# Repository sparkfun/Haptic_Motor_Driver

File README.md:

SparkFun Haptic Motor Driver
========================================

[*SparkFun Haptic Motor Driver (ROB-14538)*](https://www.sparkfun.com/products/14538)
	
Ready to add some good vibes to your project? Look no further than the SparkFun Haptic Motor Driver. This board breaks out Texas Instruments' DRV2605L Haptic Motor Driver, which adds meaningful feedback from your devices using the breakout and an Arduino-compatible device.

The DRV2605L is capable of driving two different types of motors, ERM and LRA. It is important to know, however, that the default firmware for the DRV2605L is set for use with ERM type motors. We have created an Arduino library that makes the DRV2605L easy to use with six different ERM effects and one LRA effect.
	
The SparkFun Haptic Motor Driver breakout board features six pins to provide power to the sensor and I2C bus. Additionally, a microcontroller that supports I2C is required to communicate with the DRV2605L and relay the data to the user by means of vibration.

Repository Contents	
---------------	

* **/Documentation** - Data sheets, additional product information, ZIP folder containing all project files and a ZIP folder containing libraries and example code 
* **/Hardware** - Eagle design files (.brd, .sch)
* **/Libraries** - Libraries for use with the Haptic Motor Driver with some example projects 
* **/Production** - Production panel files (.brd)

Documentation
---------------	

* **[Library](https://github.com/sparkfun/SparkFun_Haptic_Motor_Driver_Arduino_Library)** - Arduino-compatible library for the Haptic Motor Driver.
* **[Hookup Guide](https://learn.sparkfun.com/tutorials/haptic-motor-driver-hook-up-guide)** - Basic hookup guide for the Haptic Motor driver.
* **[SparkFun Fritzing repo](https://github.com/sparkfun/Fritzing_Parts)** - Fritzing diagrams for SparkFun products.

Product Versions
---------------

* [ROB-14538](https://www.sparkfun.com/products/retired/14538)- v20
* [ROB-14031](https://www.sparkfun.com/products/retired/14031)- v10

Version History
---------------

* [v20](https://github.com/sparkfun/Haptic_Motor_Driver/releases/tag/v20) - v20
* [v10](https://github.com/sparkfun/Haptic_Motor_Driver/releases/tag/v10) - Initial release

License Information
---------------

This product is _**open source**_! 

Please review the LICENSE.md file for license information. 

If you have any questions or concerns on licensing, please contact techsupport@sparkfun.com.

Distributed as-is; no warranty is given.

- Your friends at SparkFun.

_<COLLABORATION CREDIT>_

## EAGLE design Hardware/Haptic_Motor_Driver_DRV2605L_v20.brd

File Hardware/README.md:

SparkFun DRV2605L Haptic Motor Driver Design Files
=====================================

The .sch and .brd files hare are Eagle CAD schematic and PCB design files from SparkFun Electronics.
A freeware version of Eagle can be found [here](http://www.cadsoftusa.com/download-eagle/freeware/).

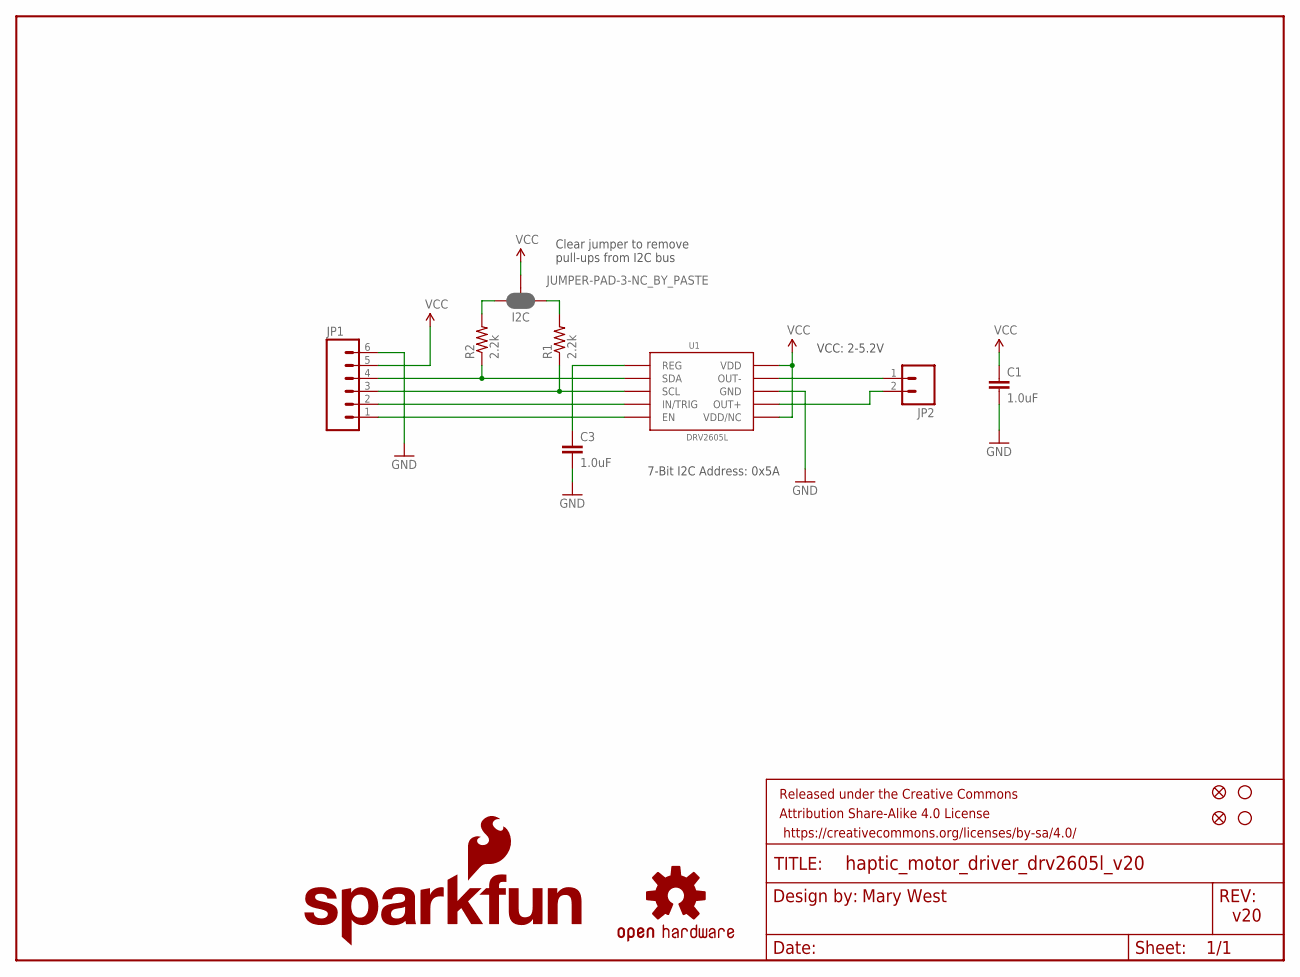
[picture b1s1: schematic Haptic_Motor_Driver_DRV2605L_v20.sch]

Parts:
C1, C3: 1.0uF; 0402-CAP
FID1, FID2: FIDUCIAL1X2; FIDUCIAL-1X2
FRAME2: FRAME-LETTER; CREATIVE_COMMONS
I2C: JUMPER-PAD-3-NC_BY_PASTE; PAD-JUMPER-3-NC_BY_PASTE_YES_SILK_FULL_BOX
JP1: M06SILK_FEMALE_PTH; 1X06
JP2: M02PTH; 1X02
LOGO2: OSHW-LOGOS; OSHW-LOGO-S
LOGO4: SFE_LOGO_NAME_FLAME.1_INCH; SFE_LOGO_NAME_FLAME_.1
R1, R2: 2.2k; 0603-RES
STANDOFF1, STANDOFF4: STAND-OFF
U1: DRV2605L; VSSOP-10

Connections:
GND: C1.2, C3.2, JP1.6, U1.P$8 (GND)
unnamed: JP1.4, R2.1, U1.P$3 (SDA)
unnamed: JP1.3, R1.1, U1.P$2 (SCL)
unnamed: C3.1, U1.P$1 (REG)
unnamed: JP1.2, U1.P$4 (IN/TRIG)
unnamed: JP1.1, U1.P$5 (EN)
unnamed: JP2.1, U1.P$9 (OUT-)
unnamed: JP2.2, U1.P$7 (OUT+)
unnamed: I2C.3, R2.2
unnamed: I2C.1, R1.2
VCC: C1.1, I2C.2, JP1.5, U1.P$6 (VDD/NC), U1.P$10 (VDD)

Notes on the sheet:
7-Bit I2C Address: 0x5A
VCC: 2-5.2V
Clear jumper to remove pull-ups from I2C bus
v20
Mary West

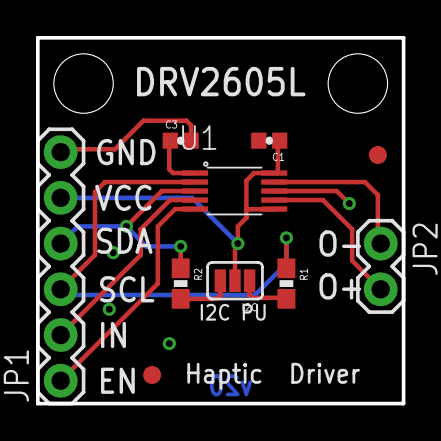
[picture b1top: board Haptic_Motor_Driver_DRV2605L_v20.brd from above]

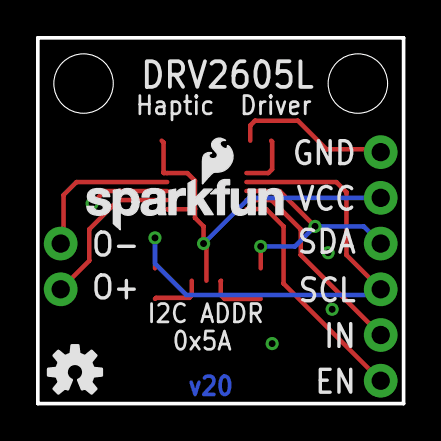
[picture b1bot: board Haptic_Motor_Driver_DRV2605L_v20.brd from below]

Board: 2 copper layers, 20.3 x 20.3 mm, 15 parts (2 on the bottom side), 11 nets.

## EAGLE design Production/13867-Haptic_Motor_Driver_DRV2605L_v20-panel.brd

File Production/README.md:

SparkFun DRV2605L Haptic Motor Driver Production Files
=========================================

These are the production files SparkFun uses for printing PCBs.

License Information
-------------------
This product is open source! 

The hardware is released under [Creative Commons ShareAlike 4.0 International](https://creativecommons.org/licenses/by-sa/4.0/).

Please use, reuse, and modify these files as you see fit. Please maintain attribution to SparkFun Electronics and release anything derivative under the same license.

Distributed as-is; no warranty is given.

- Your friends at SparkFun.

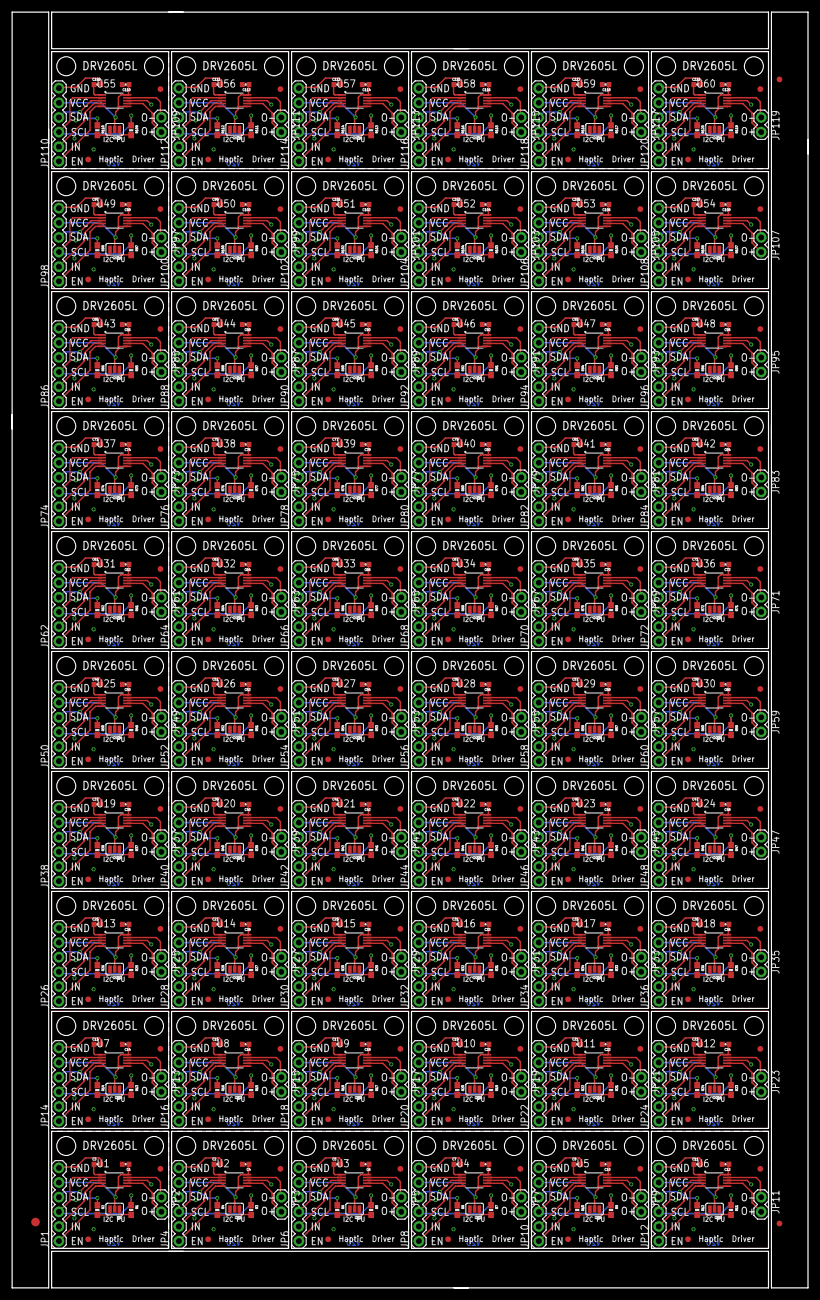
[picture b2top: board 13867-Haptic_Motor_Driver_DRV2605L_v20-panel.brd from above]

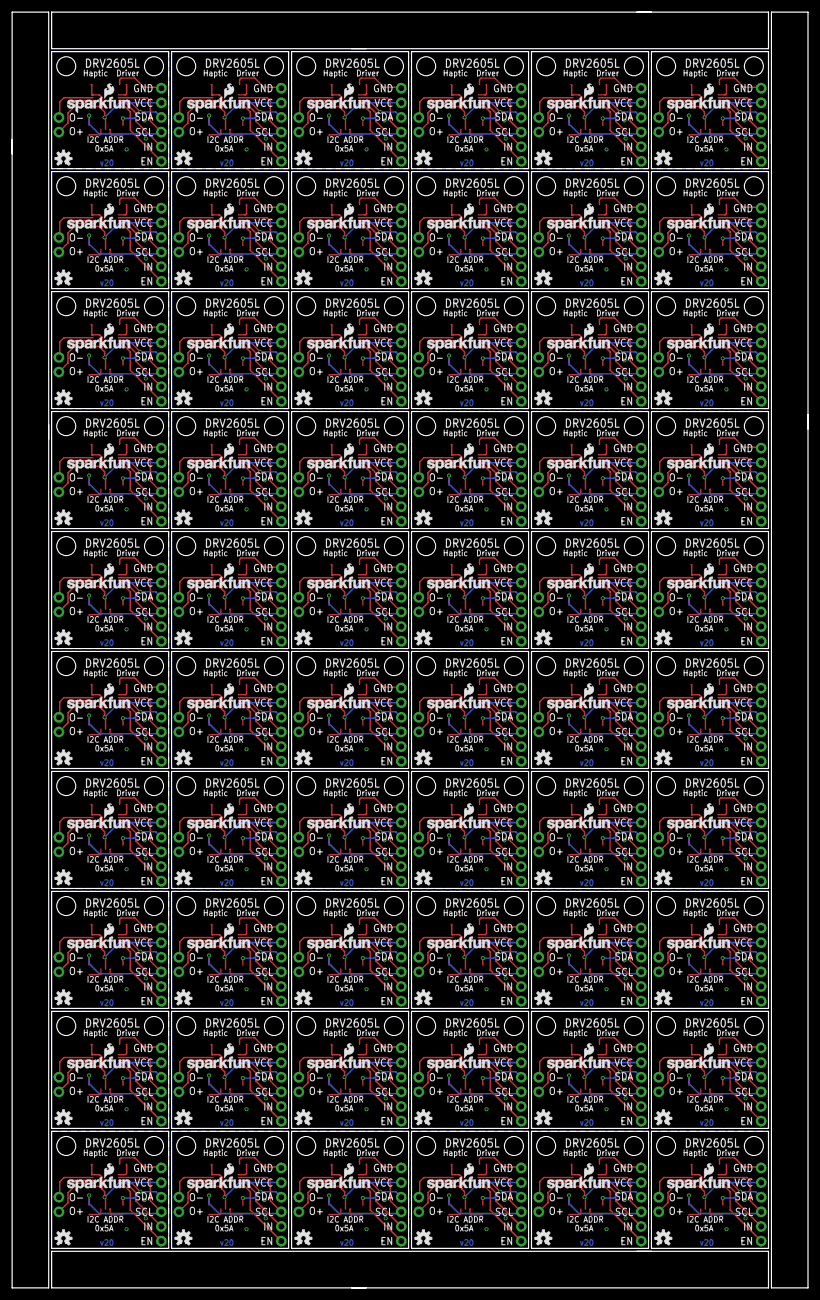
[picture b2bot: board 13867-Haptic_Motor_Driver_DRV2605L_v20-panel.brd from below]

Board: 2 copper layers, 138.2 x 221.5 mm, 843 parts (120 on the bottom side), 660 nets.

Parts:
C1, C2, C3, C4, C5, C6, C7, C8, C9, C10, C11, C12, C13, C14, C15, C16, C17, C18, C19, C20, C21, C22, C23, C24, C25, C26, C27, C28, C29, C30, C31, C32, C33, C34, C35, C36, C37, C38, C39, C40, C41, C42, C43, C44, C45, C46, C47, C48, C49, C50, C51, C52, C53, C54, C55, C56, C57, C58, C59, C60, C61, C62, C63, C64, C65, C66, C67, C68, C69, C70, C71, C72, C73, C74, C75, C76, C77, C78, C79, C80, C81, C82, C83, C84, C85, C86, C87, C88, C89, C90, C91, C92, C93, C94, C95, C96, C97, C98, C99, C100, C101, C102, C103, C104, C105, C106, C107, C108, C109, C110, C111, C112, C113, C114, C115, C116, C117, C118, C119, C120: 1.0uF; 0402-CAP
E$1: FIDUCIAL-1.5X3
E$5, E$6: FIDUCIAL-1X2
FID1, FID2, FID3, FID4, FID5, FID6, FID7, FID8, FID9, FID10, FID11, FID12, FID13, FID14, FID15, FID16, FID17, FID18, FID19, FID20, FID21, FID22, FID23, FID24, FID25, FID26, FID27, FID28, FID29, FID30, FID31, FID32, FID33, FID34, FID35, FID36, FID37, FID38, FID39, FID40, FID41, FID42, FID43, FID44, FID45, FID46, FID47, FID48, FID49, FID50, FID51, FID52, FID53, FID54, FID55, FID56, FID57, FID58, FID59, FID60, FID61, FID62, FID63, FID64, FID65, FID66, FID67, FID68, FID69, FID70, FID71, FID72, FID73, FID74, FID75, FID76, FID77, FID78, FID79, FID80, FID81, FID82, FID83, FID84, FID85, FID86, FID87, FID88, FID89, FID90, FID91, FID92, FID93, FID94, FID95, FID96, FID97, FID98, FID99, FID100, FID101, FID102, FID103, FID104, FID105, FID106, FID107, FID108, FID109, FID110, FID111, FID112, FID113, FID114, FID115, FID116, FID117, FID118, FID119, FID120: FIDUCIAL1X2; FIDUCIAL-1X2
I2C, I2C1, I2C2, I2C3, I2C4, I2C5, I2C6, I2C7, I2C8, I2C9, I2C10, I2C11, I2C12, I2C13, I2C14, I2C15, I2C16, I2C17, I2C18, I2C19, I2C20, I2C21, I2C22, I2C23, I2C24, I2C25, I2C26, I2C27, I2C28, I2C29, I2C30, I2C31, I2C32, I2C33, I2C34, I2C35, I2C36, I2C37, I2C38, I2C39, I2C40, I2C41, I2C42, I2C43, I2C44, I2C45, I2C46, I2C47, I2C48, I2C49, I2C50, I2C51, I2C52, I2C53, I2C54, I2C55, I2C56, I2C57, I2C58, I2C59: JUMPER-PAD-3-NC_BY_PASTE; PAD-JUMPER-3-NC_BY_PASTE_YES_SILK_FULL_BOX
JP1, JP4, JP6, JP8, JP10, JP12, JP14, JP16, JP18, JP20, JP22, JP24, JP26, JP28, JP30, JP32, JP34, JP36, JP38, JP40, JP42, JP44, JP46, JP48, JP50, JP52, JP54, JP56, JP58, JP60, JP62, JP64, JP66, JP68, JP70, JP72, JP74, JP76, JP78, JP80, JP82, JP84, JP86, JP88, JP90, JP92, JP94, JP96, JP98, JP100, JP102, JP104, JP106, JP108, JP110, JP112, JP114, JP116, JP118, JP120: 1X06
JP2, JP3, JP5, JP7, JP9, JP11, JP13, JP15, JP17, JP19, JP21, JP23, JP25, JP27, JP29, JP31, JP33, JP35, JP37, JP39, JP41, JP43, JP45, JP47, JP49, JP51, JP53, JP55, JP57, JP59, JP61, JP63, JP65, JP67, JP69, JP71, JP73, JP75, JP77, JP79, JP81, JP83, JP85, JP87, JP89, JP91, JP93, JP95, JP97, JP99, JP101, JP103, JP105, JP107, JP109, JP111, JP113, JP115, JP117, JP119: 1X02
LOGO1, LOGO2, LOGO5, LOGO7, LOGO9, LOGO11, LOGO13, LOGO15, LOGO17, LOGO19, LOGO21, LOGO23, LOGO25, LOGO27, LOGO29, LOGO31, LOGO33, LOGO35, LOGO37, LOGO39, LOGO41, LOGO43, LOGO45, LOGO47, LOGO49, LOGO51, LOGO53, LOGO55, LOGO57, LOGO59, LOGO61, LOGO63, LOGO65, LOGO67, LOGO69, LOGO71, LOGO73, LOGO75, LOGO77, LOGO79, LOGO81, LOGO83, LOGO85, LOGO87, LOGO89, LOGO91, LOGO93, LOGO95, LOGO97, LOGO99, LOGO101, LOGO103, LOGO105, LOGO107, LOGO109, LOGO111, LOGO113, LOGO115, LOGO117, LOGO119: OSHW-LOGOS; OSHW-LOGO-S
LOGO3, LOGO4, LOGO6, LOGO8, LOGO10, LOGO12, LOGO14, LOGO16, LOGO18, LOGO20, LOGO22, LOGO24, LOGO26, LOGO28, LOGO30, LOGO32, LOGO34, LOGO36, LOGO38, LOGO40, LOGO42, LOGO44, LOGO46, LOGO48, LOGO50, LOGO52, LOGO54, LOGO56, LOGO58, LOGO60, LOGO62, LOGO64, LOGO66, LOGO68, LOGO70, LOGO72, LOGO74, LOGO76, LOGO78, LOGO80, LOGO82, LOGO84, LOGO86, LOGO88, LOGO90, LOGO92, LOGO94, LOGO96, LOGO98, LOGO100, LOGO102, LOGO104, LOGO106, LOGO108, LOGO110, LOGO112, LOGO114, LOGO116, LOGO118, LOGO120: SFE_LOGO_NAME_FLAME.1_INCH; SFE_LOGO_NAME_FLAME_.1
R1, R2, R3, R4, R5, R6, R7, R8, R9, R10, R11, R12, R13, R14, R15, R16, R17, R18, R19, R20, R21, R22, R23, R24, R25, R26, R27, R28, R29, R30, R31, R32, R33, R34, R35, R36, R37, R38, R39, R40, R41, R42, R43, R44, R45, R46, R47, R48, R49, R50, R51, R52, R53, R54, R55, R56, R57, R58, R59, R60, R61, R62, R63, R64, R65, R66, R67, R68, R69, R70, R71, R72, R73, R74, R75, R76, R77, R78, R79, R80, R81, R82, R83, R84, R85, R86, R87, R88, R89, R90, R91, R92, R93, R94, R95, R96, R97, R98, R99, R100, R101, R102, R103, R104, R105, R106, R107, R108, R109, R110, R111, R112, R113, R114, R115, R116, R117, R118, R119, R120: 2.2k; 0603-RES
STANDOFF1, STANDOFF2, STANDOFF3, STANDOFF4, STANDOFF5, STANDOFF6, STANDOFF7, STANDOFF8, STANDOFF9, STANDOFF10, STANDOFF11, STANDOFF12, STANDOFF13, STANDOFF14, STANDOFF15, STANDOFF16, STANDOFF17, STANDOFF18, STANDOFF19, STANDOFF20, STANDOFF21, STANDOFF22, STANDOFF23, STANDOFF24, STANDOFF25, STANDOFF26, STANDOFF27, STANDOFF28, STANDOFF29, STANDOFF30, STANDOFF31, STANDOFF32, STANDOFF33, STANDOFF34, STANDOFF35, STANDOFF36, STANDOFF37, STANDOFF38, STANDOFF39, STANDOFF40, STANDOFF41, STANDOFF42, STANDOFF43, STANDOFF44, STANDOFF45, STANDOFF46, STANDOFF47, STANDOFF48, STANDOFF49, STANDOFF50, STANDOFF51, STANDOFF52, STANDOFF53, STANDOFF54, STANDOFF55, STANDOFF56, STANDOFF57, STANDOFF58, STANDOFF59, STANDOFF60, STANDOFF61, STANDOFF62, STANDOFF63, STANDOFF64, STANDOFF65, STANDOFF66, STANDOFF67, STANDOFF68, STANDOFF69, STANDOFF70, STANDOFF71, STANDOFF72, STANDOFF73, STANDOFF74, STANDOFF75, STANDOFF76, STANDOFF77, STANDOFF78, STANDOFF79, STANDOFF80, STANDOFF81, STANDOFF82, STANDOFF83, STANDOFF84, STANDOFF85, STANDOFF86, STANDOFF87, STANDOFF88, STANDOFF89, STANDOFF90, STANDOFF91, STANDOFF92, STANDOFF93, STANDOFF94, STANDOFF95, STANDOFF96, STANDOFF97, STANDOFF98, STANDOFF99, STANDOFF100, STANDOFF101, STANDOFF102, STANDOFF103, STANDOFF104, STANDOFF105, STANDOFF106, STANDOFF107, STANDOFF108, STANDOFF109, STANDOFF110, STANDOFF111, STANDOFF112, STANDOFF113, STANDOFF114, STANDOFF115, STANDOFF116, STANDOFF117, STANDOFF118, STANDOFF119, STANDOFF120: STAND-OFF
U1, U2, U3, U4, U5, U6, U7, U8, U9, U10, U11, U12, U13, U14, U15, U16, U17, U18, U19, U20, U21, U22, U23, U24, U25, U26, U27, U28, U29, U30, U31, U32, U33, U34, U35, U36, U37, U38, U39, U40, U41, U42, U43, U44, U45, U46, U47, U48, U49, U50, U51, U52, U53, U54, U55, U56, U57, U58, U59, U60: DRV2605L; VSSOP-10

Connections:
GND: C1.2, C3.2, JP1.6, U1.P$8
GND1: C2.2, C4.2, JP4.6, U2.P$8
GND2: C5.2, C6.2, JP6.6, U3.P$8
GND3: C7.2, C8.2, JP8.6, U4.P$8
GND4: C9.2, C10.2, JP10.6, U5.P$8
GND5: C11.2, C12.2, JP12.6, U6.P$8
GND6: C13.2, C14.2, JP14.6, U7.P$8
GND7: C15.2, C16.2, JP16.6, U8.P$8
GND8: C17.2, C18.2, JP18.6, U9.P$8
GND9: C19.2, C20.2, JP20.6, U10.P$8
GND10: C21.2, C22.2, JP22.6, U11.P$8
GND11: C23.2, C24.2, JP24.6, U12.P$8
GND12: C25.2, C26.2, JP26.6, U13.P$8
GND13: C27.2, C28.2, JP28.6, U14.P$8
GND14: C29.2, C30.2, JP30.6, U15.P$8
GND15: C31.2, C32.2, JP32.6, U16.P$8
GND16: C33.2, C34.2, JP34.6, U17.P$8
GND17: C35.2, C36.2, JP36.6, U18.P$8
GND18: C37.2, C38.2, JP38.6, U19.P$8
GND19: C39.2, C40.2, JP40.6, U20.P$8
GND20: C41.2, C42.2, JP42.6, U21.P$8
GND21: C43.2, C44.2, JP44.6, U22.P$8
GND22: C45.2, C46.2, JP46.6, U23.P$8
GND23: C47.2, C48.2, JP48.6, U24.P$8
GND24: C49.2, C50.2, JP50.6, U25.P$8
GND25: C51.2, C52.2, JP52.6, U26.P$8
GND26: C53.2, C54.2, JP54.6, U27.P$8
GND27: C55.2, C56.2, JP56.6, U28.P$8
GND28: C57.2, C58.2, JP58.6, U29.P$8
GND29: C59.2, C60.2, JP60.6, U30.P$8
GND30: C61.2, C62.2, JP62.6, U31.P$8
GND31: C63.2, C64.2, JP64.6, U32.P$8
GND32: C65.2, C66.2, JP66.6, U33.P$8
GND33: C67.2, C68.2, JP68.6, U34.P$8
GND34: C69.2, C70.2, JP70.6, U35.P$8
GND35: C71.2, C72.2, JP72.6, U36.P$8
GND36: C73.2, C74.2, JP74.6, U37.P$8
GND37: C75.2, C76.2, JP76.6, U38.P$8
GND38: C77.2, C78.2, JP78.6, U39.P$8
GND39: C79.2, C80.2, JP80.6, U40.P$8
GND40: C81.2, C82.2, JP82.6, U41.P$8
GND41: C83.2, C84.2, JP84.6, U42.P$8
GND42: C85.2, C86.2, JP86.6, U43.P$8
GND43: C87.2, C88.2, JP88.6, U44.P$8
GND44: C89.2, C90.2, JP90.6, U45.P$8
GND45: C91.2, C92.2, JP92.6, U46.P$8
GND46: C93.2, C94.2, JP94.6, U47.P$8
GND47: C95.2, C96.2, JP96.6, U48.P$8
GND48: C97.2, C98.2, JP98.6, U49.P$8
GND49: C99.2, C100.2, JP100.6, U50.P$8
GND50: C101.2, C102.2, JP102.6, U51.P$8
GND51: C103.2, C104.2, JP104.6, U52.P$8
GND52: C105.2, C106.2, JP106.6, U53.P$8
GND53: C107.2, C108.2, JP108.6, U54.P$8
GND54: C109.2, C110.2, JP110.6, U55.P$8
GND55: C111.2, C112.2, JP112.6, U56.P$8
GND56: C113.2, C114.2, JP114.6, U57.P$8
GND57: C115.2, C116.2, JP116.6, U58.P$8
GND58: C117.2, C118.2, JP118.6, U59.P$8
GND59: C119.2, C120.2, JP120.6, U60.P$8
unnamed: JP1.4, R2.1, U1.P$3
unnamed: JP1.3, R1.1, U1.P$2
unnamed: C3.1, U1.P$1
unnamed: JP1.2, U1.P$4
unnamed: JP1.1, U1.P$5
unnamed: JP2.1, U1.P$9
unnamed: JP2.2, U1.P$7
unnamed: I2C.3, R2.2
unnamed: I2C.1, R1.2
unnamed: C2.1, U2.P$1
unnamed: JP4.2, U2.P$4
unnamed: JP4.1, U2.P$5
unnamed: JP3.1, U2.P$9
unnamed: JP3.2, U2.P$7
unnamed: I2C1.3, R4.2
unnamed: I2C1.1, R3.2
unnamed: JP4.4, R4.1, U2.P$3
unnamed: JP4.3, R3.1, U2.P$2
unnamed: C5.1, U3.P$1
unnamed: JP6.2, U3.P$4
unnamed: JP6.1, U3.P$5
unnamed: JP5.1, U3.P$9
unnamed: JP5.2, U3.P$7
unnamed: I2C2.3, R6.2
unnamed: I2C2.1, R5.2
unnamed: JP6.4, R6.1, U3.P$3
unnamed: JP6.3, R5.1, U3.P$2
unnamed: C7.1, U4.P$1
unnamed: JP8.2, U4.P$4
unnamed: JP8.1, U4.P$5
unnamed: JP7.1, U4.P$9
unnamed: JP7.2, U4.P$7
unnamed: I2C3.3, R8.2
unnamed: I2C3.1, R7.2
unnamed: JP8.4, R8.1, U4.P$3
unnamed: JP8.3, R7.1, U4.P$2
unnamed: C9.1, U5.P$1
unnamed: JP10.2, U5.P$4
unnamed: JP10.1, U5.P$5
unnamed: JP9.1, U5.P$9
unnamed: JP9.2, U5.P$7
unnamed: I2C4.3, R10.2
unnamed: I2C4.1, R9.2
unnamed: JP10.4, R10.1, U5.P$3
unnamed: JP10.3, R9.1, U5.P$2
unnamed: C11.1, U6.P$1
unnamed: JP12.2, U6.P$4
unnamed: JP12.1, U6.P$5
unnamed: JP11.1, U6.P$9
unnamed: JP11.2, U6.P$7
unnamed: I2C5.3, R12.2
unnamed: I2C5.1, R11.2
unnamed: JP12.4, R12.1, U6.P$3
unnamed: JP12.3, R11.1, U6.P$2
unnamed: C13.1, U7.P$1
unnamed: JP14.2, U7.P$4
unnamed: JP14.1, U7.P$5
unnamed: JP13.1, U7.P$9
unnamed: JP13.2, U7.P$7
unnamed: I2C6.3, R14.2
unnamed: I2C6.1, R13.2
unnamed: JP14.4, R14.1, U7.P$3
unnamed: JP14.3, R13.1, U7.P$2
unnamed: C15.1, U8.P$1
unnamed: JP16.2, U8.P$4
unnamed: JP16.1, U8.P$5
unnamed: JP15.1, U8.P$9
unnamed: JP15.2, U8.P$7
unnamed: I2C7.3, R16.2
unnamed: I2C7.1, R15.2
unnamed: JP16.4, R16.1, U8.P$3
unnamed: JP16.3, R15.1, U8.P$2
unnamed: C17.1, U9.P$1
unnamed: JP18.2, U9.P$4
unnamed: JP18.1, U9.P$5
unnamed: JP17.1, U9.P$9
unnamed: JP17.2, U9.P$7
unnamed: I2C8.3, R18.2
unnamed: I2C8.1, R17.2
unnamed: JP18.4, R18.1, U9.P$3
unnamed: JP18.3, R17.1, U9.P$2
unnamed: C19.1, U10.P$1
unnamed: JP20.2, U10.P$4
unnamed: JP20.1, U10.P$5
unnamed: JP19.1, U10.P$9
unnamed: JP19.2, U10.P$7
unnamed: I2C9.3, R20.2
unnamed: I2C9.1, R19.2
unnamed: JP20.4, R20.1, U10.P$3
unnamed: JP20.3, R19.1, U10.P$2
unnamed: C21.1, U11.P$1
unnamed: JP22.2, U11.P$4
unnamed: JP22.1, U11.P$5
unnamed: JP21.1, U11.P$9
unnamed: JP21.2, U11.P$7
unnamed: I2C10.3, R22.2
unnamed: I2C10.1, R21.2
unnamed: JP22.4, R22.1, U11.P$3
unnamed: JP22.3, R21.1, U11.P$2
unnamed: C23.1, U12.P$1
unnamed: JP24.2, U12.P$4
unnamed: JP24.1, U12.P$5
unnamed: JP23.1, U12.P$9
unnamed: JP23.2, U12.P$7
unnamed: I2C11.3, R24.2
unnamed: I2C11.1, R23.2
unnamed: JP24.4, R24.1, U12.P$3
unnamed: JP24.3, R23.1, U12.P$2
unnamed: C25.1, U13.P$1
unnamed: JP26.2, U13.P$4
unnamed: JP26.1, U13.P$5
unnamed: JP25.1, U13.P$9
unnamed: JP25.2, U13.P$7
unnamed: I2C12.3, R26.2
unnamed: I2C12.1, R25.2
unnamed: JP26.4, R26.1, U13.P$3
unnamed: JP26.3, R25.1, U13.P$2
unnamed: C27.1, U14.P$1
unnamed: JP28.2, U14.P$4
unnamed: JP28.1, U14.P$5
unnamed: JP27.1, U14.P$9
unnamed: JP27.2, U14.P$7
unnamed: I2C13.3, R28.2
unnamed: I2C13.1, R27.2
unnamed: JP28.4, R28.1, U14.P$3
unnamed: JP28.3, R27.1, U14.P$2
unnamed: C29.1, U15.P$1
unnamed: JP30.2, U15.P$4
unnamed: JP30.1, U15.P$5
unnamed: JP29.1, U15.P$9
unnamed: JP29.2, U15.P$7
unnamed: I2C14.3, R30.2
unnamed: I2C14.1, R29.2
unnamed: JP30.4, R30.1, U15.P$3
unnamed: JP30.3, R29.1, U15.P$2
unnamed: C31.1, U16.P$1
unnamed: JP32.2, U16.P$4
unnamed: JP32.1, U16.P$5
unnamed: JP31.1, U16.P$9
unnamed: JP31.2, U16.P$7
unnamed: I2C15.3, R32.2
unnamed: I2C15.1, R31.2
unnamed: JP32.4, R32.1, U16.P$3
unnamed: JP32.3, R31.1, U16.P$2
unnamed: C33.1, U17.P$1
unnamed: JP34.2, U17.P$4
unnamed: JP34.1, U17.P$5
unnamed: JP33.1, U17.P$9
unnamed: JP33.2, U17.P$7
unnamed: I2C16.3, R34.2
unnamed: I2C16.1, R33.2
unnamed: JP34.4, R34.1, U17.P$3
unnamed: JP34.3, R33.1, U17.P$2
unnamed: C35.1, U18.P$1
unnamed: JP36.2, U18.P$4
unnamed: JP36.1, U18.P$5
unnamed: JP35.1, U18.P$9
unnamed: JP35.2, U18.P$7
unnamed: I2C17.3, R36.2
unnamed: I2C17.1, R35.2
unnamed: JP36.4, R36.1, U18.P$3
unnamed: JP36.3, R35.1, U18.P$2
unnamed: C37.1, U19.P$1
unnamed: JP38.2, U19.P$4
unnamed: JP38.1, U19.P$5
unnamed: JP37.1, U19.P$9
unnamed: JP37.2, U19.P$7
unnamed: I2C18.3, R38.2
unnamed: I2C18.1, R37.2
unnamed: JP38.4, R38.1, U19.P$3
unnamed: JP38.3, R37.1, U19.P$2
unnamed: C39.1, U20.P$1
unnamed: JP40.2, U20.P$4
unnamed: JP40.1, U20.P$5
unnamed: JP39.1, U20.P$9
unnamed: JP39.2, U20.P$7
unnamed: I2C19.3, R40.2
unnamed: I2C19.1, R39.2
unnamed: JP40.4, R40.1, U20.P$3
unnamed: JP40.3, R39.1, U20.P$2
unnamed: C41.1, U21.P$1
unnamed: JP42.2, U21.P$4
unnamed: JP42.1, U21.P$5
unnamed: JP41.1, U21.P$9
unnamed: JP41.2, U21.P$7
unnamed: I2C20.3, R42.2
unnamed: I2C20.1, R41.2
unnamed: JP42.4, R42.1, U21.P$3
unnamed: JP42.3, R41.1, U21.P$2
unnamed: C43.1, U22.P$1
unnamed: JP44.2, U22.P$4
unnamed: JP44.1, U22.P$5
unnamed: JP43.1, U22.P$9
unnamed: JP43.2, U22.P$7
unnamed: I2C21.3, R44.2
unnamed: I2C21.1, R43.2
unnamed: JP44.4, R44.1, U22.P$3
unnamed: JP44.3, R43.1, U22.P$2
unnamed: C45.1, U23.P$1
unnamed: JP46.2, U23.P$4
unnamed: JP46.1, U23.P$5
unnamed: JP45.1, U23.P$9
unnamed: JP45.2, U23.P$7
unnamed: I2C22.3, R46.2
unnamed: I2C22.1, R45.2
unnamed: JP46.4, R46.1, U23.P$3
unnamed: JP46.3, R45.1, U23.P$2
unnamed: C47.1, U24.P$1
unnamed: JP48.2, U24.P$4
unnamed: JP48.1, U24.P$5
unnamed: JP47.1, U24.P$9
unnamed: JP47.2, U24.P$7
unnamed: I2C23.3, R48.2
unnamed: I2C23.1, R47.2
unnamed: JP48.4, R48.1, U24.P$3
unnamed: JP48.3, R47.1, U24.P$2
unnamed: C49.1, U25.P$1
unnamed: JP50.2, U25.P$4
unnamed: JP50.1, U25.P$5
unnamed: JP49.1, U25.P$9
unnamed: JP49.2, U25.P$7
unnamed: I2C24.3, R50.2
unnamed: I2C24.1, R49.2
unnamed: JP50.4, R50.1, U25.P$3
unnamed: JP50.3, R49.1, U25.P$2
unnamed: C51.1, U26.P$1
unnamed: JP52.2, U26.P$4
unnamed: JP52.1, U26.P$5
unnamed: JP51.1, U26.P$9
unnamed: JP51.2, U26.P$7
unnamed: I2C25.3, R52.2
unnamed: I2C25.1, R51.2
unnamed: JP52.4, R52.1, U26.P$3
unnamed: JP52.3, R51.1, U26.P$2
unnamed: C53.1, U27.P$1
unnamed: JP54.2, U27.P$4
unnamed: JP54.1, U27.P$5
unnamed: JP53.1, U27.P$9
unnamed: JP53.2, U27.P$7
unnamed: I2C26.3, R54.2
unnamed: I2C26.1, R53.2
unnamed: JP54.4, R54.1, U27.P$3
unnamed: JP54.3, R53.1, U27.P$2
unnamed: C55.1, U28.P$1
unnamed: JP56.2, U28.P$4
unnamed: JP56.1, U28.P$5
unnamed: JP55.1, U28.P$9
unnamed: JP55.2, U28.P$7
unnamed: I2C27.3, R56.2
unnamed: I2C27.1, R55.2
unnamed: JP56.4, R56.1, U28.P$3
unnamed: JP56.3, R55.1, U28.P$2
unnamed: C57.1, U29.P$1
unnamed: JP58.2, U29.P$4
unnamed: JP58.1, U29.P$5
unnamed: JP57.1, U29.P$9
unnamed: JP57.2, U29.P$7
unnamed: I2C28.3, R58.2
unnamed: I2C28.1, R57.2
unnamed: JP58.4, R58.1, U29.P$3
unnamed: JP58.3, R57.1, U29.P$2
unnamed: C59.1, U30.P$1
unnamed: JP60.2, U30.P$4
unnamed: JP60.1, U30.P$5
unnamed: JP59.1, U30.P$9
unnamed: JP59.2, U30.P$7
unnamed: I2C29.3, R60.2
unnamed: I2C29.1, R59.2
unnamed: JP60.4, R60.1, U30.P$3
unnamed: JP60.3, R59.1, U30.P$2
unnamed: C61.1, U31.P$1
unnamed: JP62.2, U31.P$4
unnamed: JP62.1, U31.P$5
unnamed: JP61.1, U31.P$9
unnamed: JP61.2, U31.P$7
unnamed: I2C30.3, R62.2
unnamed: I2C30.1, R61.2
unnamed: JP62.4, R62.1, U31.P$3
unnamed: JP62.3, R61.1, U31.P$2
unnamed: C63.1, U32.P$1
unnamed: JP64.2, U32.P$4
unnamed: JP64.1, U32.P$5
unnamed: JP63.1, U32.P$9
unnamed: JP63.2, U32.P$7
unnamed: I2C31.3, R64.2
unnamed: I2C31.1, R63.2
unnamed: JP64.4, R64.1, U32.P$3
unnamed: JP64.3, R63.1, U32.P$2
unnamed: C65.1, U33.P$1
unnamed: JP66.2, U33.P$4
unnamed: JP66.1, U33.P$5
unnamed: JP65.1, U33.P$9
unnamed: JP65.2, U33.P$7
unnamed: I2C32.3, R66.2
unnamed: I2C32.1, R65.2
unnamed: JP66.4, R66.1, U33.P$3
unnamed: JP66.3, R65.1, U33.P$2
unnamed: C67.1, U34.P$1
unnamed: JP68.2, U34.P$4
unnamed: JP68.1, U34.P$5
unnamed: JP67.1, U34.P$9
unnamed: JP67.2, U34.P$7
unnamed: I2C33.3, R68.2
unnamed: I2C33.1, R67.2
unnamed: JP68.4, R68.1, U34.P$3
unnamed: JP68.3, R67.1, U34.P$2
unnamed: C69.1, U35.P$1
unnamed: JP70.2, U35.P$4
unnamed: JP70.1, U35.P$5
unnamed: JP69.1, U35.P$9
unnamed: JP69.2, U35.P$7
unnamed: I2C34.3, R70.2
unnamed: I2C34.1, R69.2
unnamed: JP70.4, R70.1, U35.P$3
unnamed: JP70.3, R69.1, U35.P$2
unnamed: C71.1, U36.P$1
unnamed: JP72.2, U36.P$4
unnamed: JP72.1, U36.P$5
unnamed: JP71.1, U36.P$9
unnamed: JP71.2, U36.P$7
unnamed: I2C35.3, R72.2
unnamed: I2C35.1, R71.2
unnamed: JP72.4, R72.1, U36.P$3
unnamed: JP72.3, R71.1, U36.P$2
unnamed: C73.1, U37.P$1
unnamed: JP74.2, U37.P$4
unnamed: JP74.1, U37.P$5
unnamed: JP73.1, U37.P$9
unnamed: JP73.2, U37.P$7
unnamed: I2C36.3, R74.2
unnamed: I2C36.1, R73.2
unnamed: JP74.4, R74.1, U37.P$3
unnamed: JP74.3, R73.1, U37.P$2
unnamed: C75.1, U38.P$1
unnamed: JP76.2, U38.P$4
unnamed: JP76.1, U38.P$5
unnamed: JP75.1, U38.P$9
unnamed: JP75.2, U38.P$7
unnamed: I2C37.3, R76.2
unnamed: I2C37.1, R75.2
unnamed: JP76.4, R76.1, U38.P$3
unnamed: JP76.3, R75.1, U38.P$2
unnamed: C77.1, U39.P$1
unnamed: JP78.2, U39.P$4
unnamed: JP78.1, U39.P$5
unnamed: JP77.1, U39.P$9
unnamed: JP77.2, U39.P$7
unnamed: I2C38.3, R78.2
unnamed: I2C38.1, R77.2
unnamed: JP78.4, R78.1, U39.P$3
unnamed: JP78.3, R77.1, U39.P$2
unnamed: C79.1, U40.P$1
unnamed: JP80.2, U40.P$4
unnamed: JP80.1, U40.P$5
unnamed: JP79.1, U40.P$9
unnamed: JP79.2, U40.P$7
unnamed: I2C39.3, R80.2
unnamed: I2C39.1, R79.2
unnamed: JP80.4, R80.1, U40.P$3
unnamed: JP80.3, R79.1, U40.P$2
unnamed: C81.1, U41.P$1
unnamed: JP82.2, U41.P$4
unnamed: JP82.1, U41.P$5
unnamed: JP81.1, U41.P$9
unnamed: JP81.2, U41.P$7
unnamed: I2C40.3, R82.2
unnamed: I2C40.1, R81.2
unnamed: JP82.4, R82.1, U41.P$3
unnamed: JP82.3, R81.1, U41.P$2
unnamed: C83.1, U42.P$1
unnamed: JP84.2, U42.P$4
unnamed: JP84.1, U42.P$5
unnamed: JP83.1, U42.P$9
unnamed: JP83.2, U42.P$7
unnamed: I2C41.3, R84.2
unnamed: I2C41.1, R83.2
unnamed: JP84.4, R84.1, U42.P$3
unnamed: JP84.3, R83.1, U42.P$2
unnamed: C85.1, U43.P$1
unnamed: JP86.2, U43.P$4
unnamed: JP86.1, U43.P$5
unnamed: JP85.1, U43.P$9
unnamed: JP85.2, U43.P$7
unnamed: I2C42.3, R86.2
unnamed: I2C42.1, R85.2
unnamed: JP86.4, R86.1, U43.P$3
unnamed: JP86.3, R85.1, U43.P$2
unnamed: C87.1, U44.P$1
unnamed: JP88.2, U44.P$4
unnamed: JP88.1, U44.P$5
unnamed: JP87.1, U44.P$9
unnamed: JP87.2, U44.P$7
unnamed: I2C43.3, R88.2
unnamed: I2C43.1, R87.2
unnamed: JP88.4, R88.1, U44.P$3
unnamed: JP88.3, R87.1, U44.P$2
unnamed: C89.1, U45.P$1
unnamed: JP90.2, U45.P$4
unnamed: JP90.1, U45.P$5
unnamed: JP89.1, U45.P$9
unnamed: JP89.2, U45.P$7
unnamed: I2C44.3, R90.2
unnamed: I2C44.1, R89.2
unnamed: JP90.4, R90.1, U45.P$3
unnamed: JP90.3, R89.1, U45.P$2
unnamed: C91.1, U46.P$1
unnamed: JP92.2, U46.P$4
unnamed: JP92.1, U46.P$5
unnamed: JP91.1, U46.P$9
unnamed: JP91.2, U46.P$7
unnamed: I2C45.3, R92.2
unnamed: I2C45.1, R91.2
unnamed: JP92.4, R92.1, U46.P$3
unnamed: JP92.3, R91.1, U46.P$2
unnamed: C93.1, U47.P$1
unnamed: JP94.2, U47.P$4
unnamed: JP94.1, U47.P$5
unnamed: JP93.1, U47.P$9
unnamed: JP93.2, U47.P$7
unnamed: I2C46.3, R94.2
unnamed: I2C46.1, R93.2
unnamed: JP94.4, R94.1, U47.P$3
unnamed: JP94.3, R93.1, U47.P$2
unnamed: C95.1, U48.P$1
unnamed: JP96.2, U48.P$4
unnamed: JP96.1, U48.P$5
unnamed: JP95.1, U48.P$9
unnamed: JP95.2, U48.P$7
unnamed: I2C47.3, R96.2
unnamed: I2C47.1, R95.2
unnamed: JP96.4, R96.1, U48.P$3
unnamed: JP96.3, R95.1, U48.P$2
unnamed: C97.1, U49.P$1
unnamed: JP98.2, U49.P$4
unnamed: JP98.1, U49.P$5
unnamed: JP97.1, U49.P$9
unnamed: JP97.2, U49.P$7
unnamed: I2C48.3, R98.2
unnamed: I2C48.1, R97.2
unnamed: JP98.4, R98.1, U49.P$3
unnamed: JP98.3, R97.1, U49.P$2
unnamed: C99.1, U50.P$1
unnamed: JP100.2, U50.P$4
unnamed: JP100.1, U50.P$5
unnamed: JP99.1, U50.P$9
unnamed: JP99.2, U50.P$7
unnamed: I2C49.3, R100.2
unnamed: I2C49.1, R99.2
unnamed: JP100.4, R100.1, U50.P$3
unnamed: JP100.3, R99.1, U50.P$2
unnamed: C101.1, U51.P$1
unnamed: JP102.2, U51.P$4
unnamed: JP102.1, U51.P$5
unnamed: JP101.1, U51.P$9
unnamed: JP101.2, U51.P$7
unnamed: I2C50.3, R102.2
unnamed: I2C50.1, R101.2
unnamed: JP102.4, R102.1, U51.P$3
unnamed: JP102.3, R101.1, U51.P$2
unnamed: C103.1, U52.P$1
unnamed: JP104.2, U52.P$4
unnamed: JP104.1, U52.P$5
unnamed: JP103.1, U52.P$9
unnamed: JP103.2, U52.P$7
unnamed: I2C51.3, R104.2
unnamed: I2C51.1, R103.2
unnamed: JP104.4, R104.1, U52.P$3
unnamed: JP104.3, R103.1, U52.P$2
unnamed: C105.1, U53.P$1
unnamed: JP106.2, U53.P$4
unnamed: JP106.1, U53.P$5
unnamed: JP105.1, U53.P$9
unnamed: JP105.2, U53.P$7
unnamed: I2C52.3, R106.2
unnamed: I2C52.1, R105.2
unnamed: JP106.4, R106.1, U53.P$3
unnamed: JP106.3, R105.1, U53.P$2
unnamed: C107.1, U54.P$1
unnamed: JP108.2, U54.P$4
unnamed: JP108.1, U54.P$5
unnamed: JP107.1, U54.P$9
unnamed: JP107.2, U54.P$7
unnamed: I2C53.3, R108.2
unnamed: I2C53.1, R107.2
unnamed: JP108.4, R108.1, U54.P$3
unnamed: JP108.3, R107.1, U54.P$2
unnamed: C109.1, U55.P$1
unnamed: JP110.2, U55.P$4
unnamed: JP110.1, U55.P$5
unnamed: JP109.1, U55.P$9
unnamed: JP109.2, U55.P$7
unnamed: I2C54.3, R110.2
unnamed: I2C54.1, R109.2
unnamed: JP110.4, R110.1, U55.P$3
unnamed: JP110.3, R109.1, U55.P$2
unnamed: C111.1, U56.P$1
unnamed: JP112.2, U56.P$4
unnamed: JP112.1, U56.P$5
unnamed: JP111.1, U56.P$9
unnamed: JP111.2, U56.P$7
unnamed: I2C55.3, R112.2
unnamed: I2C55.1, R111.2
unnamed: JP112.4, R112.1, U56.P$3
unnamed: JP112.3, R111.1, U56.P$2
unnamed: C113.1, U57.P$1
unnamed: JP114.2, U57.P$4
unnamed: JP114.1, U57.P$5
unnamed: JP113.1, U57.P$9
unnamed: JP113.2, U57.P$7
unnamed: I2C56.3, R114.2
unnamed: I2C56.1, R113.2
unnamed: JP114.4, R114.1, U57.P$3
unnamed: JP114.3, R113.1, U57.P$2
unnamed: C115.1, U58.P$1
unnamed: JP116.2, U58.P$4
unnamed: JP116.1, U58.P$5
unnamed: JP115.1, U58.P$9
unnamed: JP115.2, U58.P$7
unnamed: I2C57.3, R116.2
unnamed: I2C57.1, R115.2
unnamed: JP116.4, R116.1, U58.P$3
unnamed: JP116.3, R115.1, U58.P$2
unnamed: C117.1, U59.P$1
unnamed: JP118.2, U59.P$4
unnamed: JP118.1, U59.P$5
unnamed: JP117.1, U59.P$9
unnamed: JP117.2, U59.P$7
unnamed: I2C58.3, R118.2
unnamed: I2C58.1, R117.2
unnamed: JP118.4, R118.1, U59.P$3
unnamed: JP118.3, R117.1, U59.P$2
unnamed: C119.1, U60.P$1
unnamed: JP120.2, U60.P$4
unnamed: JP120.1, U60.P$5
unnamed: JP119.1, U60.P$9
unnamed: JP119.2, U60.P$7
unnamed: I2C59.3, R120.2
unnamed: I2C59.1, R119.2
unnamed: JP120.4, R120.1, U60.P$3
unnamed: JP120.3, R119.1, U60.P$2
VCC: C1.1, I2C.2, JP1.5, U1.P$6, U1.P$10
VCC1: C4.1, I2C1.2, JP4.5, U2.P$6, U2.P$10
VCC2: C6.1, I2C2.2, JP6.5, U3.P$6, U3.P$10
VCC3: C8.1, I2C3.2, JP8.5, U4.P$6, U4.P$10
VCC4: C10.1, I2C4.2, JP10.5, U5.P$6, U5.P$10
VCC5: C12.1, I2C5.2, JP12.5, U6.P$6, U6.P$10
VCC6: C14.1, I2C6.2, JP14.5, U7.P$6, U7.P$10
VCC7: C16.1, I2C7.2, JP16.5, U8.P$6, U8.P$10
VCC8: C18.1, I2C8.2, JP18.5, U9.P$6, U9.P$10
VCC9: C20.1, I2C9.2, JP20.5, U10.P$6, U10.P$10
VCC10: C22.1, I2C10.2, JP22.5, U11.P$6, U11.P$10
VCC11: C24.1, I2C11.2, JP24.5, U12.P$6, U12.P$10
VCC12: C26.1, I2C12.2, JP26.5, U13.P$6, U13.P$10
VCC13: C28.1, I2C13.2, JP28.5, U14.P$6, U14.P$10
VCC14: C30.1, I2C14.2, JP30.5, U15.P$6, U15.P$10
VCC15: C32.1, I2C15.2, JP32.5, U16.P$6, U16.P$10
VCC16: C34.1, I2C16.2, JP34.5, U17.P$6, U17.P$10
VCC17: C36.1, I2C17.2, JP36.5, U18.P$6, U18.P$10
VCC18: C38.1, I2C18.2, JP38.5, U19.P$6, U19.P$10
VCC19: C40.1, I2C19.2, JP40.5, U20.P$6, U20.P$10
VCC20: C42.1, I2C20.2, JP42.5, U21.P$6, U21.P$10
VCC21: C44.1, I2C21.2, JP44.5, U22.P$6, U22.P$10
VCC22: C46.1, I2C22.2, JP46.5, U23.P$6, U23.P$10
VCC23: C48.1, I2C23.2, JP48.5, U24.P$6, U24.P$10
VCC24: C50.1, I2C24.2, JP50.5, U25.P$6, U25.P$10
VCC25: C52.1, I2C25.2, JP52.5, U26.P$6, U26.P$10
VCC26: C54.1, I2C26.2, JP54.5, U27.P$6, U27.P$10
VCC27: C56.1, I2C27.2, JP56.5, U28.P$6, U28.P$10
VCC28: C58.1, I2C28.2, JP58.5, U29.P$6, U29.P$10
VCC29: C60.1, I2C29.2, JP60.5, U30.P$6, U30.P$10
VCC30: C62.1, I2C30.2, JP62.5, U31.P$6, U31.P$10
VCC31: C64.1, I2C31.2, JP64.5, U32.P$6, U32.P$10
VCC32: C66.1, I2C32.2, JP66.5, U33.P$6, U33.P$10
VCC33: C68.1, I2C33.2, JP68.5, U34.P$6, U34.P$10
VCC34: C70.1, I2C34.2, JP70.5, U35.P$6, U35.P$10
VCC35: C72.1, I2C35.2, JP72.5, U36.P$6, U36.P$10
VCC36: C74.1, I2C36.2, JP74.5, U37.P$6, U37.P$10
VCC37: C76.1, I2C37.2, JP76.5, U38.P$6, U38.P$10
VCC38: C78.1, I2C38.2, JP78.5, U39.P$6, U39.P$10
VCC39: C80.1, I2C39.2, JP80.5, U40.P$6, U40.P$10
VCC40: C82.1, I2C40.2, JP82.5, U41.P$6, U41.P$10
VCC41: C84.1, I2C41.2, JP84.5, U42.P$6, U42.P$10
VCC42: C86.1, I2C42.2, JP86.5, U43.P$6, U43.P$10
VCC43: C88.1, I2C43.2, JP88.5, U44.P$6, U44.P$10
VCC44: C90.1, I2C44.2, JP90.5, U45.P$6, U45.P$10
VCC45: C92.1, I2C45.2, JP92.5, U46.P$6, U46.P$10
VCC46: C94.1, I2C46.2, JP94.5, U47.P$6, U47.P$10
VCC47: C96.1, I2C47.2, JP96.5, U48.P$6, U48.P$10
VCC48: C98.1, I2C48.2, JP98.5, U49.P$6, U49.P$10
VCC49: C100.1, I2C49.2, JP100.5, U50.P$6, U50.P$10
VCC50: C102.1, I2C50.2, JP102.5, U51.P$6, U51.P$10
VCC51: C104.1, I2C51.2, JP104.5, U52.P$6, U52.P$10
VCC52: C106.1, I2C52.2, JP106.5, U53.P$6, U53.P$10
VCC53: C108.1, I2C53.2, JP108.5, U54.P$6, U54.P$10
VCC54: C110.1, I2C54.2, JP110.5, U55.P$6, U55.P$10
VCC55: C112.1, I2C55.2, JP112.5, U56.P$6, U56.P$10
VCC56: C114.1, I2C56.2, JP114.5, U57.P$6, U57.P$10
VCC57: C116.1, I2C57.2, JP116.5, U58.P$6, U58.P$10
VCC58: C118.1, I2C58.2, JP118.5, U59.P$6, U59.P$10
VCC59: C120.1, I2C59.2, JP120.5, U60.P$6, U60.P$10

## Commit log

2016-10-20 First Hardware Commit
2016-10-20 Updated Per QC Checklist -- Switched SDA/SCL
2016-10-20 Updated brd file
2016-10-24 Updated BRD files per EDR
2016-10-25 Updated BRD and SCH files
2016-11-28 Updated Silk
2016-11-28 Updated Silk + Version #
2016-11-30 panel
2016-12-07 Adding firmware
2016-12-07 adding arduino sketch
2016-12-08 Adding zip file of all docs
2016-12-12 updated firmware folder
2016-12-12 updating documentation
2017-01-09 Updating src files
2017-02-01 Cleaning up Repo
2017-02-01 cleaning repo
2017-02-08 Squashed 'Libraries/Arduino/' content from commit 37daaad
    git-subtree-dir: Libraries/Arduino
    git-subtree-split: 37daaadb00fcd12ec83a43e74d469ef9acb24413
2017-02-08 update library folder
2017-02-08 Squashed 'Libraries/Arduino/' changes from 37daaad..560275c
    560275c Updated Library properties
    git-subtree-dir: Libraries/Arduino
    git-subtree-split: 560275c7c362bdfd87ca935d38d34411ea8da009
2017-11-27 Removing example
2017-11-27 Adding v20
2017-12-11 updated silk labels per QC review
2018-05-30 Triple Jumper Aperture Fix
2018-05-30 deleted floating paste square from revision

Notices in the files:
parts and their libraries:
SparkFun-Aesthetics: Licensing: CC v3.0 Share-Alike You are welcome to use this library for commercial purposes.
SparkFun-Aesthetics: Released under the Creative Commons Attribution Share-Alike 4.0 License
SparkFun-Aesthetics: Released under the Creative Commons
